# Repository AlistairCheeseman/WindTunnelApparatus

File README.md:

# WindTunnelApparatus
MENG Data Acquisition + motion control for Wind Tunnel Apparatus Project

There are three root folders in this repository:

Hardware  -  Contains hardware designs, files are created in KiCAD however relevant pdfs are provided.

Software  -  Contains software used on the Acquisition Computer

Firmware  -  Contains firmware source code, self explanatory

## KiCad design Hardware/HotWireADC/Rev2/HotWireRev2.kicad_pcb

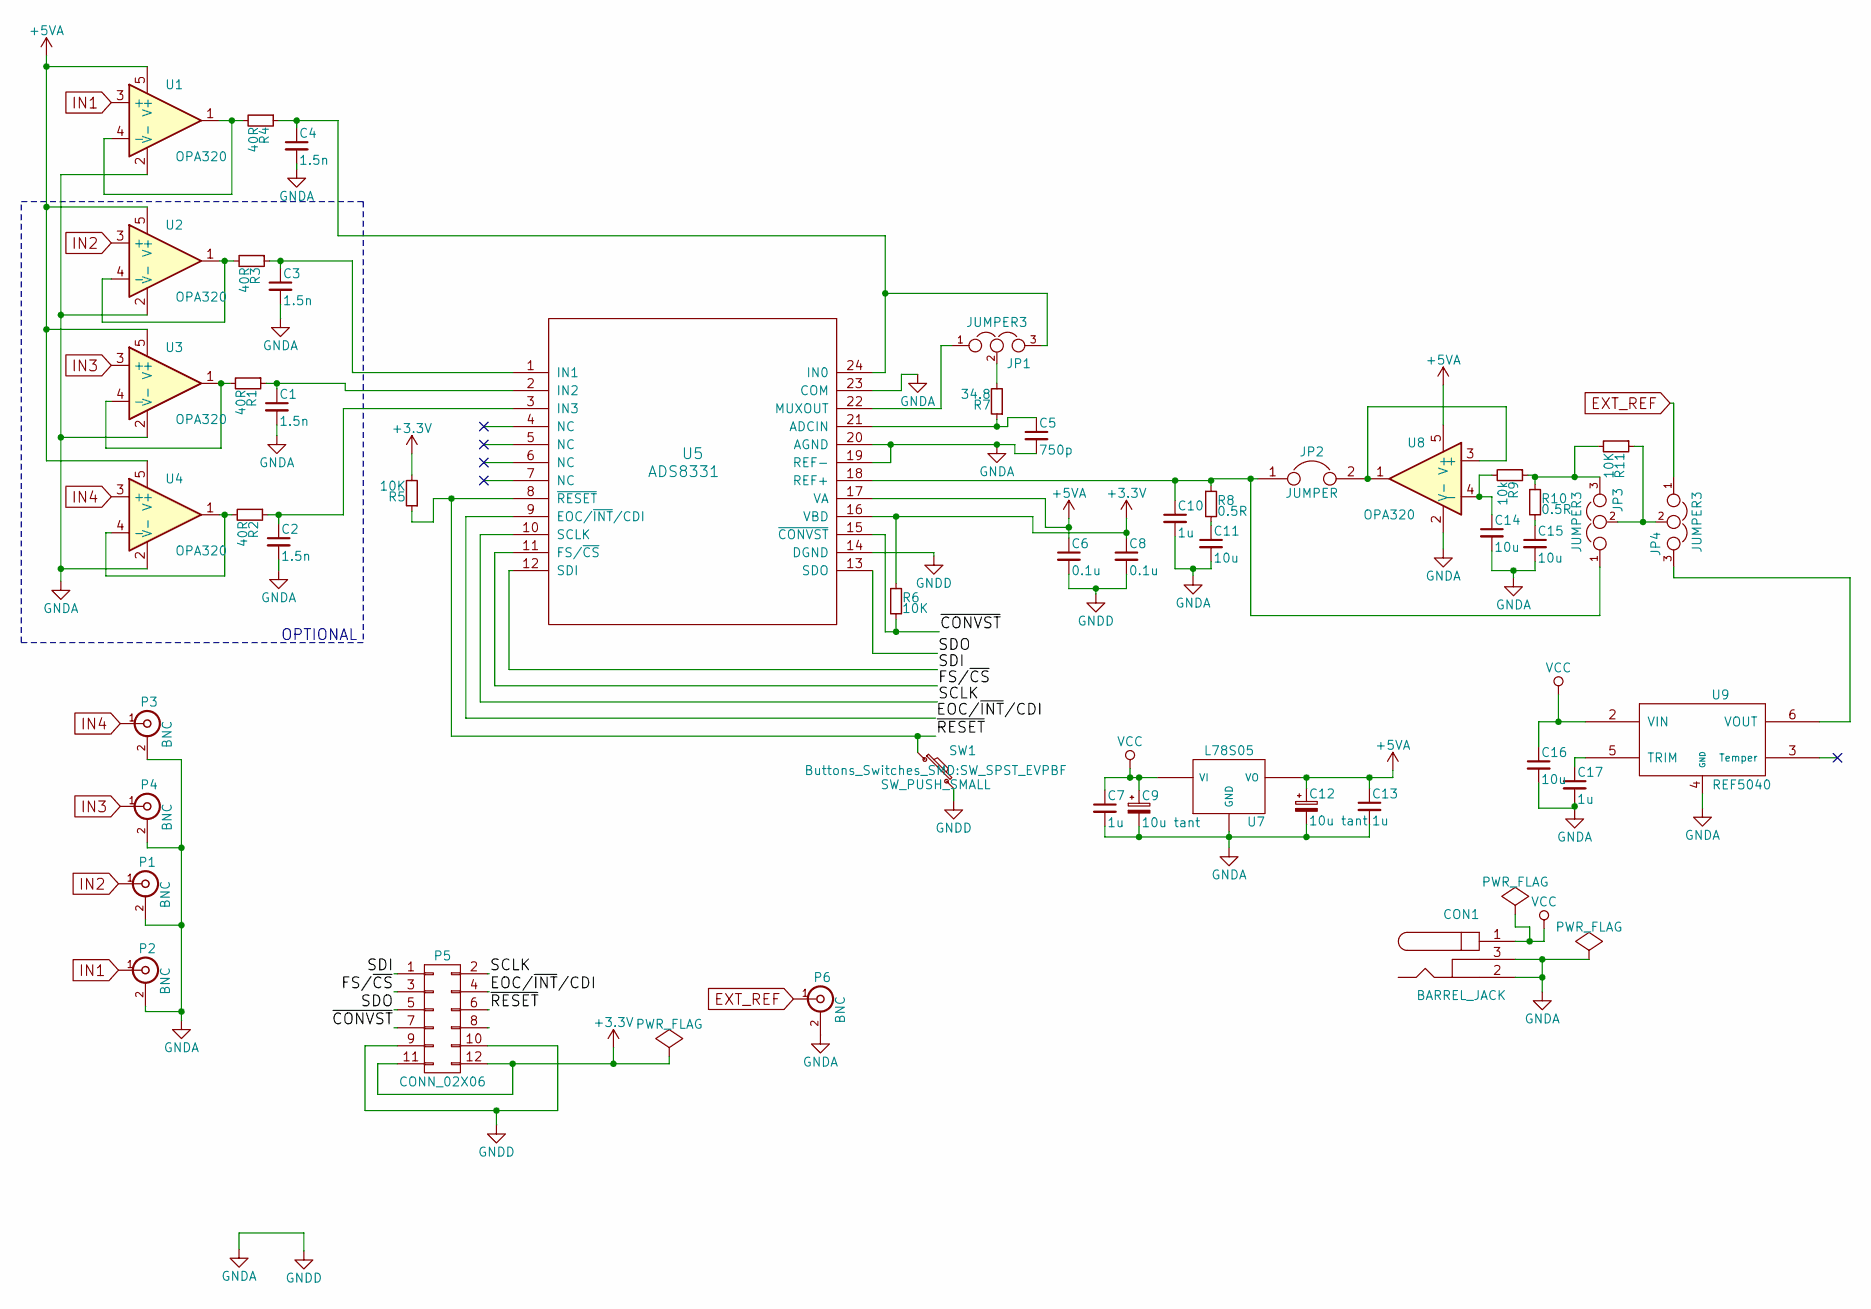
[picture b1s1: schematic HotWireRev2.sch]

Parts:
C1, C2, C3, C4: 1.5n; C_1206_HandSoldering
C5: 750p; C_1206_HandSoldering
C6, C8: 0.1u; C_1206_HandSoldering
C7, C10, C13, C17: 1u; C_1206_HandSoldering
C9, C12: 10u tant; TantalC_SizeU_EIA-6032
C11, C14, C15, C16: 10u; C_1206_HandSoldering
CON1: BARREL_JACK; JACK_SMD
JP1, JP3, JP4: JUMPER3; Socket_Strip_Straight_1x03
JP2: JUMPER; Socket_Strip_Straight_1x02
P1, P2, P3, P4, P6: BNC; bnc-ci
P5: CONN_02X06; Socket_Strip_Straight_2x06
R1, R2, R3, R4: 40R; R_1206_HandSoldering
R5, R6, R11: 10K; R_1206_HandSoldering
R7: 34.8; R_1206_HandSoldering
R8, R10: 0.5R; R_1206_HandSoldering
R9: 10k; R_1206_HandSoldering
SW1: SW_PUSH_SMALL; SW_SPST_EVPBF
U1, U2, U3, U4, U8: OPA320; SOT-23-5
U5: ADS8331; TSSOP-24_4.4x7.8mm_Pitch0.65mm
U7: L78S05; TO-220_REGULATORVIGNDVO_Vertical_LargePads
U9: REF5040; SOIC-8-N

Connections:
+3V3: C8.1, P5.11, P5.12, R5.2, R6.1, U5.16 (VBD)
+5VA: C6.1, C12.1, C13.1, U1.5 (V+), U2.5 (V+), U3.5 (V+), U4.5 (V+), U5.17 (VA), U7.VO, U8.5 (V+)
/EOC/~INT~/CDI: P5.4, U5.9 (EOC/~INT~/CDI)
/FS/~CS: P5.3, U5.11 (FS/~CS)
/SCLK: P5.2, U5.10 (SCLK)
/SDI: P5.1, U5.12 (SDI)
/SDO: P5.5, U5.13 (SDO)
/~CONVST: P5.7, R6.2, U5.15 (~CONVST)
/~RESET: P5.6, R5.1, SW1.1, U5.8 (~RESET)
EXT_REF: JP4.1, P6.1 (In)
GNDA: C1.2, C2.2, C3.2, C4.2, C5.2, C6.2, C7.2, C8.2, C9.2, C10.2, C11.2, C12.2, C13.2, C14.2, C15.2, C16.2, C17.2, CON1.2, CON1.3, P1.2 (Ext), P2.2 (Ext), P3.2 (Ext), P4.2 (Ext), P5.9, P5.10, P6.2 (Ext), SW1.2, U1.2 (V-), U2.2 (V-), U3.2 (V-), U4.2 (V-), U5.14 (DGND), U5.19 (REF-), U5.20 (AGND), U5.23 (COM), U7.GND, U8.2 (V-), U9.4 (GND)
IN1: P2.1 (In), U1.3 (+)
IN2: P1.1 (In), U2.3 (+)
IN3: P4.1 (In), U3.3 (+)
IN4: P3.1 (In), U4.3 (+)
unnamed: C1.1, R1.1, U5.2 (IN2)
unnamed: C2.1, R2.1, U5.3 (IN3)
unnamed: C3.1, R3.1, U5.1 (IN1)
unnamed: C4.1, JP1.3, R4.1, U5.24 (IN0)
unnamed: C5.1, R7.1, U5.21 (ADCIN)
unnamed: C10.1, JP2.1, JP3.1, R8.1, U5.18 (REF+)
unnamed: C11.1, R8.2
unnamed: C14.1, R9.2, U8.4 (-)
unnamed: C15.1, R10.2
unnamed: C17.1, U9.5 (TRIM)
unnamed: JP1.1, U5.22 (MUXOUT)
unnamed: JP1.2, R7.2
unnamed: JP2.2, U8.1, U8.3 (+)
unnamed: JP3.2, JP4.2, R11.1
unnamed: JP3.3, R9.1, R10.1, R11.2
unnamed: JP4.3, U9.6 (VOUT)
unnamed: R1.2, U3.1, U3.4 (-)
unnamed: R2.2, U4.1, U4.4 (-)
unnamed: R3.2, U2.1, U2.4 (-)
unnamed: R4.2, U1.1, U1.4 (-)
VCC: C7.1, C9.1, C16.1, CON1.1, U7.VI, U9.2 (VIN)

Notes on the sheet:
OPTIONAL

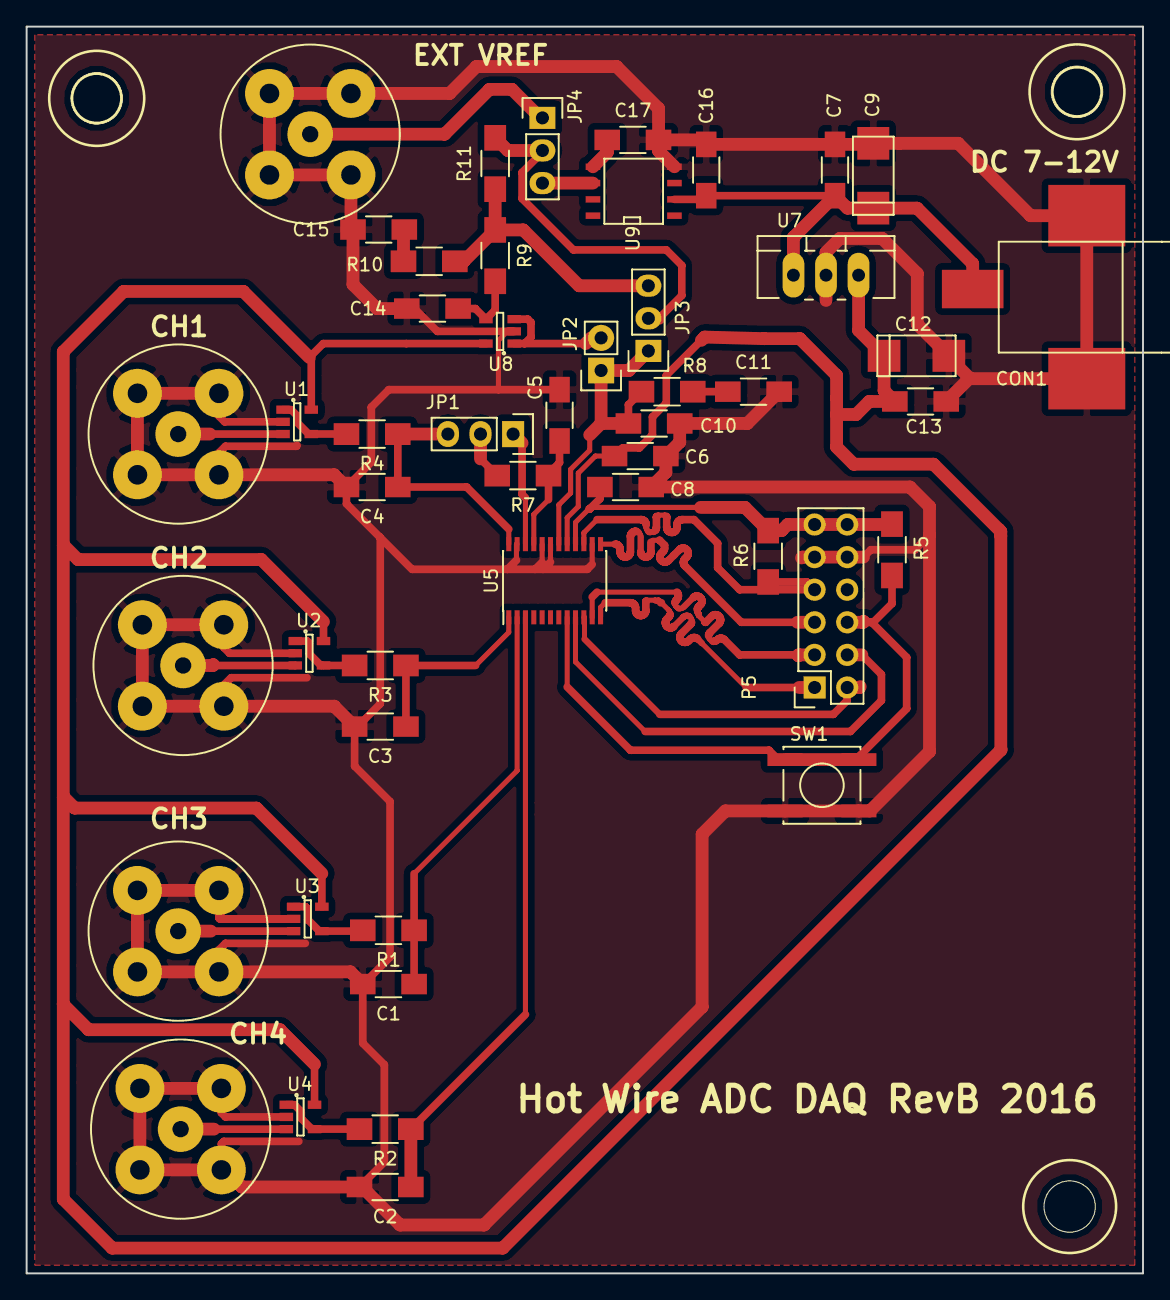
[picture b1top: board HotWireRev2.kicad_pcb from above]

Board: 2 copper layers, 87.0 x 97.2 mm, 48 parts (0 on the bottom side), 36 nets.

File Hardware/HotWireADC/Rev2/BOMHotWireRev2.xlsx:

Reference | Value | Footprint | Datasheet
U5 | ADS8331 | Housings_SSOP:TSSOP-24_4.4x7.8mm_Pitch0.65mm
JP1 | JUMPER3 | Socket_Strips:Socket_Strip_Straight_1x03 |  |  |  |  |  | Mouser Part No | Mouser Link
U1 | OPA320 | TO_SOT_Packages_SMD:SOT-23-5 |  |  |  | ADS8331 | 1 | 595-ADS8331IPW | http://www.mouser.co.uk/Search/ProductDetail.aspx?R=ADS8331I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
U2 | OPA320 | TO_SOT_Packages_SMD:SOT-23-5 |  |  |  | OPA320 | 5 | 595-OPA320AIDBVR | http://www.mouser.co.uk/Search/ProductDetail.aspx?R=OPA320AI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
U3 | OPA320 | TO_SOT_Packages_SMD:SOT-23-5 |  |  |  | 40R | 4 | #NAME?
U4 | OPA320 | TO_SOT_Packages_SMD:SOT-23-5 |  |  |  | 1.5n | 4 | 77-VJ1206Y152KXXCBC | http://www.mouser.co.uk/Search/ProductDetail.aspx?R=VJ1206Y1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
R4 | 40R | Resistors_SMD:R_1206_HandSoldering |  |  |  | 10K | 4 | 71-CRCW1206-10K-E3 | http://www.mouser.co.uk/Search/ProductDetail.aspx?R=CRCW1206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
C4 | 1.5n | Capacitors_SMD:C_1206_HandSoldering |  |  |  | 34.799999999999997 | 1 | 667-ERJ-8ENF34R8V | http://www.mouser.co.uk/Search/ProductDetail.aspx?R=ERJ-8ENF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
R3 | 40R | Resistors_SMD:R_1206_HandSoldering |  |  |  | 750p | 1 | 581-12065A751JAT2A | http://www.mouser.co.uk/Search/ProductDetail.aspx?R=12065A75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
C3 | 1.5n | Capacitors_SMD:C_1206_HandSoldering |  |  |  | SW_PUSH_SMALL | 1 | 506-2-1437565-8 | http://www.mouser.co.uk/Search/ProductDetail.aspx?R=2-143756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
R1 | 40R | Resistors_SMD:R_1206_HandSoldering |  |  |  | 0.1u | 2 | 77-VJ1206Y104KXBAT | http://www.mouser.co.uk/Search/ProductDetail.aspx?R=VJ1206Y1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
C1 | 1.5n | Capacitors_SMD:C_1206_HandSoldering |  |  |  | 1u | 4 | 77-VJ1206Y105KXQTBC | http://www.mouser.co.uk/Search/ProductDetail.aspx?R=VJ1206Y1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
R2 | 40R | Resistors_SMD:R_1206_HandSoldering |  |  |  | 10u | 4 | 77-VJ1206V106ZXQTBC | http://www.mouser.co.uk/Search/ProductDetail.aspx?R=VJ1206V1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
C2 | 1.5n | Capacitors_SMD:C_1206_HandSoldering |  |  |  | 0.5R | 2 | 603-RL1206FR070R5L | http://www.mouser.co.uk/Search/ProductDetail.aspx?R=RL1206FR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
R5 | 10K | Resistors_SMD:R_1206_HandSoldering |  |  |  | REF5040 | 1 | 595-REF5040AIDR | http://www.mouser.co.uk/Search/ProductDetail.aspx?R=REF5040A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
R7 | 34.799999999999997 | Resistors_SMD:R_1206_HandSoldering |  |  |  | 10u tant | 2 | 647-F931A106MAA | http://www.mouser.co.uk/Search/ProductDetail.aspx?R=F931A106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
C5 | 750p | Capacitors_SMD:C_1206_HandSoldering |  |  |  | L78S05 | 1 | 511-L78S05CV | http://www.mouser.co.uk/Search/ProductDetail.aspx?R=L78S05CV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
R6 | 10K | Resistors_SMD:R_1206_HandSoldering |  |  |  | BNC | 5 | 571-5-1634503-1 | http://www.mouser.co.uk/Search/ProductDetail.aspx?R=5-163450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
SW1 | SW_PUSH_SMALL | Buttons_Switches_SMD:SW_SPST_EVPBF |  |  |  | BARREL_JACK | 1 | 502-RASM712X | http://www.mouser.co.uk/Search/ProductDetail.aspx?R=RASM712X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
C8 | 0.1u | Capacitors_SMD:C_1206_HandSoldering
C6 | 0.1u | Capacitors_SMD:C_1206_HandSoldering
C10 | 1u | Capacitors_SMD:C_1206_HandSoldering
C11 | 10u | Capacitors_SMD:C_1206_HandSoldering |  |  |  | Extra filter
R8 | 0.5R | Resistors_SMD:R_1206_HandSoldering |  |  |  | 22u | 1 | 581-1206ZG226ZAT2A
JP4 | JUMPER3 | Socket_Strips:Socket_Strip_Straight_1x03 |  |  |  | 0.22Ohm | 1 | 279-RL73K2BR22JTD
JP3 | JUMPER3 | Socket_Strips:Socket_Strip_Straight_1x03
JP2 | JUMPER | Socket_Strips:Socket_Strip_Straight_1x02
U8 | OPA320 | TO_SOT_Packages_SMD:SOT-23-5 |  |  |  | Kostas BNC connector |  | 571-1-1337543-0
C14 | 10u | Capacitors_SMD:C_1206_HandSoldering
R10 | 0.5R | Resistors_SMD:R_1206_HandSoldering |  |  |  | 100ohm |  | 594-53611101
C15 | 10u | Capacitors_SMD:C_1206_HandSoldering |  |  |  | 1k |  | 858-P160KN0QD15B1K
R9 | 10k | Resistors_SMD:R_1206_HandSoldering |  |  |  | 20k |  | 858-P160KN-0QC15B20K
R11 | 10K | Resistors_SMD:R_1206_HandSoldering
U9 | REF5040 | SMD_Packages:SOIC-8-N |  |  |  | knob for pot |  | 652-H-22-6A
C17 | 1u | Capacitors_SMD:C_1206_HandSoldering
C16 | 10u | Capacitors_SMD:C_1206_HandSoldering |  |  | Rapid part no
C9 | 10u tant | Capacitors_Tantalum_SMD:TantalC_SizeU_EIA-6032 |  |  | 11-3438 | 4.7nF |  | 810-FG18X7R1H472KNT0 | http://www.mouser.co.uk/ProductDetail/TDK/FG18X7R1H472KNT00/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
C12 | 10u tant | Capacitors_Tantalum_SMD:TantalC_SizeU_EIA-6032 |  |  | 11-3436 | 2.2nf |  | 810-FG18C0G1H222JNT6 | http://www.mouser.co.uk/ProductDetail/TDK/FG18C0G1H222JNT06/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
C13 | 1u | Capacitors_SMD:C_1206_HandSoldering |  |  | 11-3433 | 470pf |  | 810-FG18C0G1H471JNT6 | http://www.mouser.co.uk/ProductDetail/TDK/FG18C0G1H471JNT06/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
C7 | 1u | Capacitors_SMD:C_1206_HandSoldering |  |  | 11-3431 | 220pf |  | 810-FG18C0G1H221JNT6 | http://www.mouser.co.uk/ProductDetail/TDK/FG18C0G1H221JNT06/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
U7 | L78S05 | CustomFootprints:TO-220_REGULATORVIGNDVO_Vertical_LargePads |  |  | 11-3409 | 150pf |  | 810-FG18C0G1H151JNT0 | http://www.mouser.co.uk/ProductDetail/TDK/FG18C0G1H151JNT00/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
P3 | BNC | Connect:bnc-ci
P4 | BNC | Connect:bnc-ci
P1 | BNC | Connect:bnc-ci
P2 | BNC | Connect:bnc-ci |  |  |  | LM555CN |  | 512-LM555CN | http://www.mouser.co.uk/ProductDetail/Fairchild-Semiconducto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
P5 | CONN_02X06 | Socket_Strips:Socket_Strip_Straight_2x06
CON1 | BARREL_JACK | Connect:JACK_ALIM
P6 | BNC | Connect:bnc-ci

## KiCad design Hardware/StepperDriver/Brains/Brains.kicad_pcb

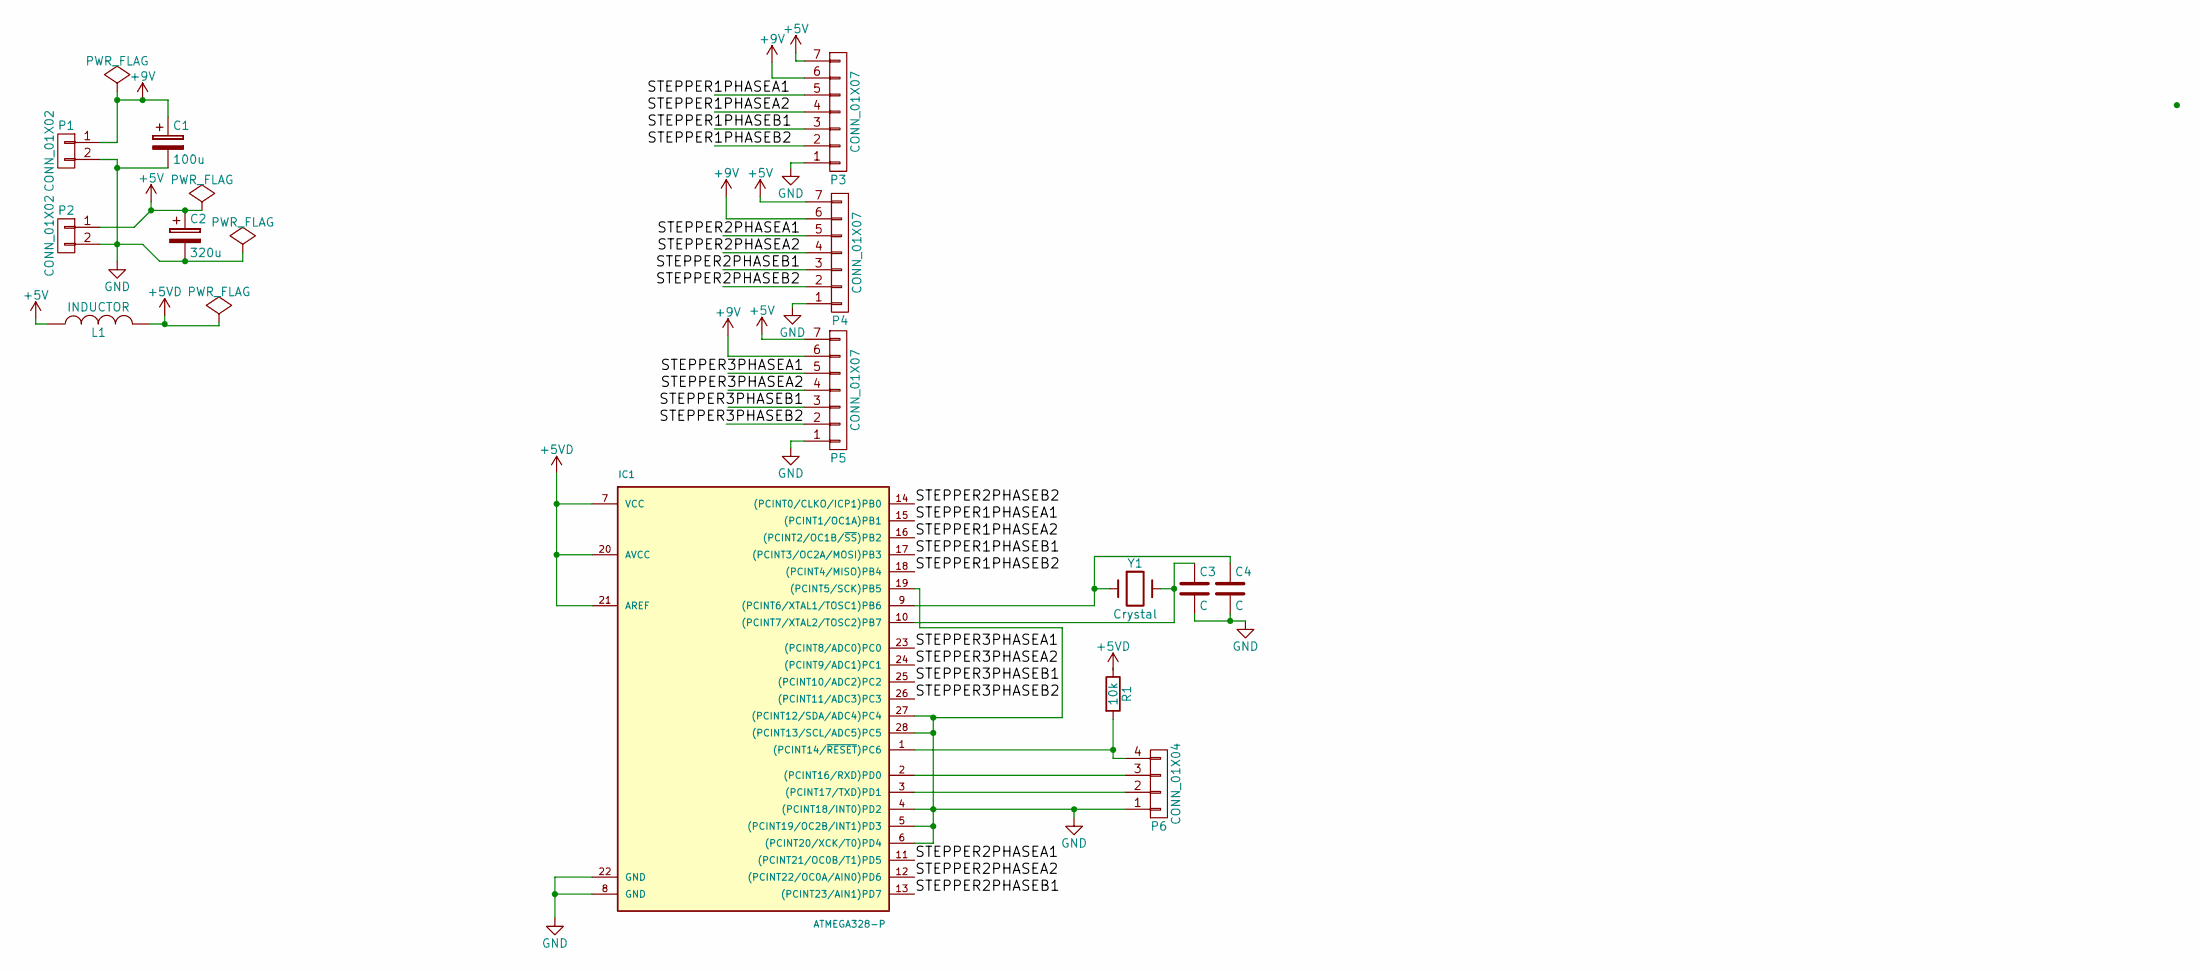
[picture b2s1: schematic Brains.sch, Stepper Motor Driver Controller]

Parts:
C1: 100u; C_Radial_D10_L20_P7.5
C2: 320u; C_Radial_D10_L20_P7.5
C3, C4: C; C_Disc_D3_P2.5
IC1: ATMEGA328-P; DIP-28_W7.62mm_LongPads
L1: INDUCTOR; Neosid_Inductor_Sd12k-style3
P1: CONN_01X02; TerminalBlock_Pheonix_MPT-2.54mm_2pol
P2: CONN_01X02; WAGO_734_2pin_Straight_RuggedPads
P3, P4, P5: CONN_01X07; Pin_Header_Straight_1x07
P6: CONN_01X04; TerminalBlock_Pheonix_MPT-2.54mm_4pol
R1: 10k; Resistor_Horizontal_RM10mm
Y1: Crystal; Crystal_HC49-U_Vertical

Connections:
+5V: C2.1, L1.1, P2.1, P3.7, P4.7, P5.7
+5VD: IC1.7 (VCC), IC1.20 (AVCC), IC1.21 (AREF), L1.2, R1.1
+9V: C1.1, P1.1, P3.6, P4.6, P5.6
/STEPPER1PHASEA1: IC1.15 ((PCINT1/OC1A)PB1), P3.5
/STEPPER1PHASEA2: IC1.16 ((PCINT2/OC1B/~SS~)PB2), P3.4
/STEPPER1PHASEB1: IC1.17 ((PCINT3/OC2A/MOSI)PB3), P3.3
/STEPPER1PHASEB2: IC1.18 ((PCINT4/MISO)PB4), P3.2
/STEPPER2PHASEA1: IC1.11 ((PCINT21/OC0B/T1)PD5), P4.5
/STEPPER2PHASEA2: IC1.12 ((PCINT22/OC0A/AIN0)PD6), P4.4
/STEPPER2PHASEB1: IC1.13 ((PCINT23/AIN1)PD7), P4.3
/STEPPER2PHASEB2: IC1.14 ((PCINT0/CLKO/ICP1)PB0), P4.2
/STEPPER3PHASEA1: IC1.23 ((PCINT8/ADC0)PC0), P5.5
/STEPPER3PHASEA2: IC1.24 ((PCINT9/ADC1)PC1), P5.4
/STEPPER3PHASEB1: IC1.25 ((PCINT10/ADC2)PC2), P5.3
/STEPPER3PHASEB2: IC1.26 ((PCINT11/ADC3)PC3), P5.2
GND: C1.2, C2.2, C3.2, C4.2, IC1.4 ((PCINT18/INT0)PD2), IC1.5 ((PCINT19/OC2B/INT1)PD3), IC1.6 ((PCINT20/XCK/T0)PD4), IC1.8 (GND), IC1.19 ((PCINT5/SCK)PB5), IC1.22 (GND), IC1.27 ((PCINT12/SDA/ADC4)PC4), IC1.28 ((PCINT13/SCL/ADC5)PC5), P1.2, P2.2, P3.1, P4.1, P5.1, P6.1
unnamed: C3.1, IC1.10 ((PCINT7/XTAL2/TOSC2)PB7), Y1.2
unnamed: C4.1, IC1.9 ((PCINT6/XTAL1/TOSC1)PB6), Y1.1
unnamed: IC1.1 ((PCINT14/~RESET~)PC6), P6.4, R1.2
unnamed: IC1.2 ((PCINT16/RXD)PD0), P6.3
unnamed: IC1.3 ((PCINT17/TXD)PD1), P6.2

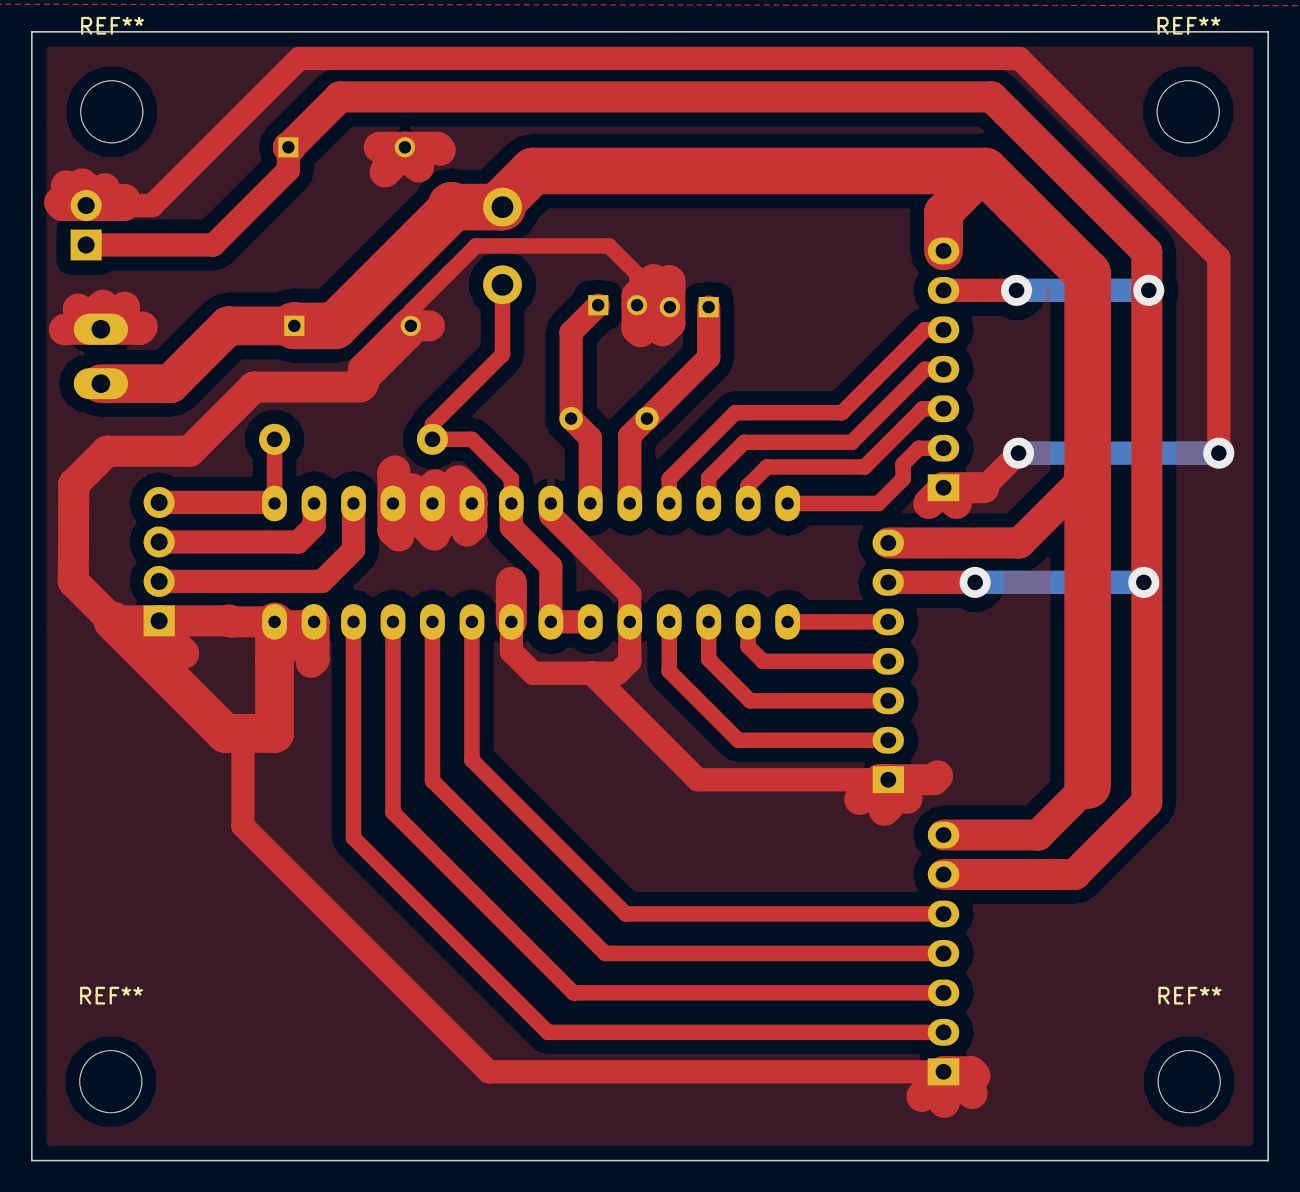
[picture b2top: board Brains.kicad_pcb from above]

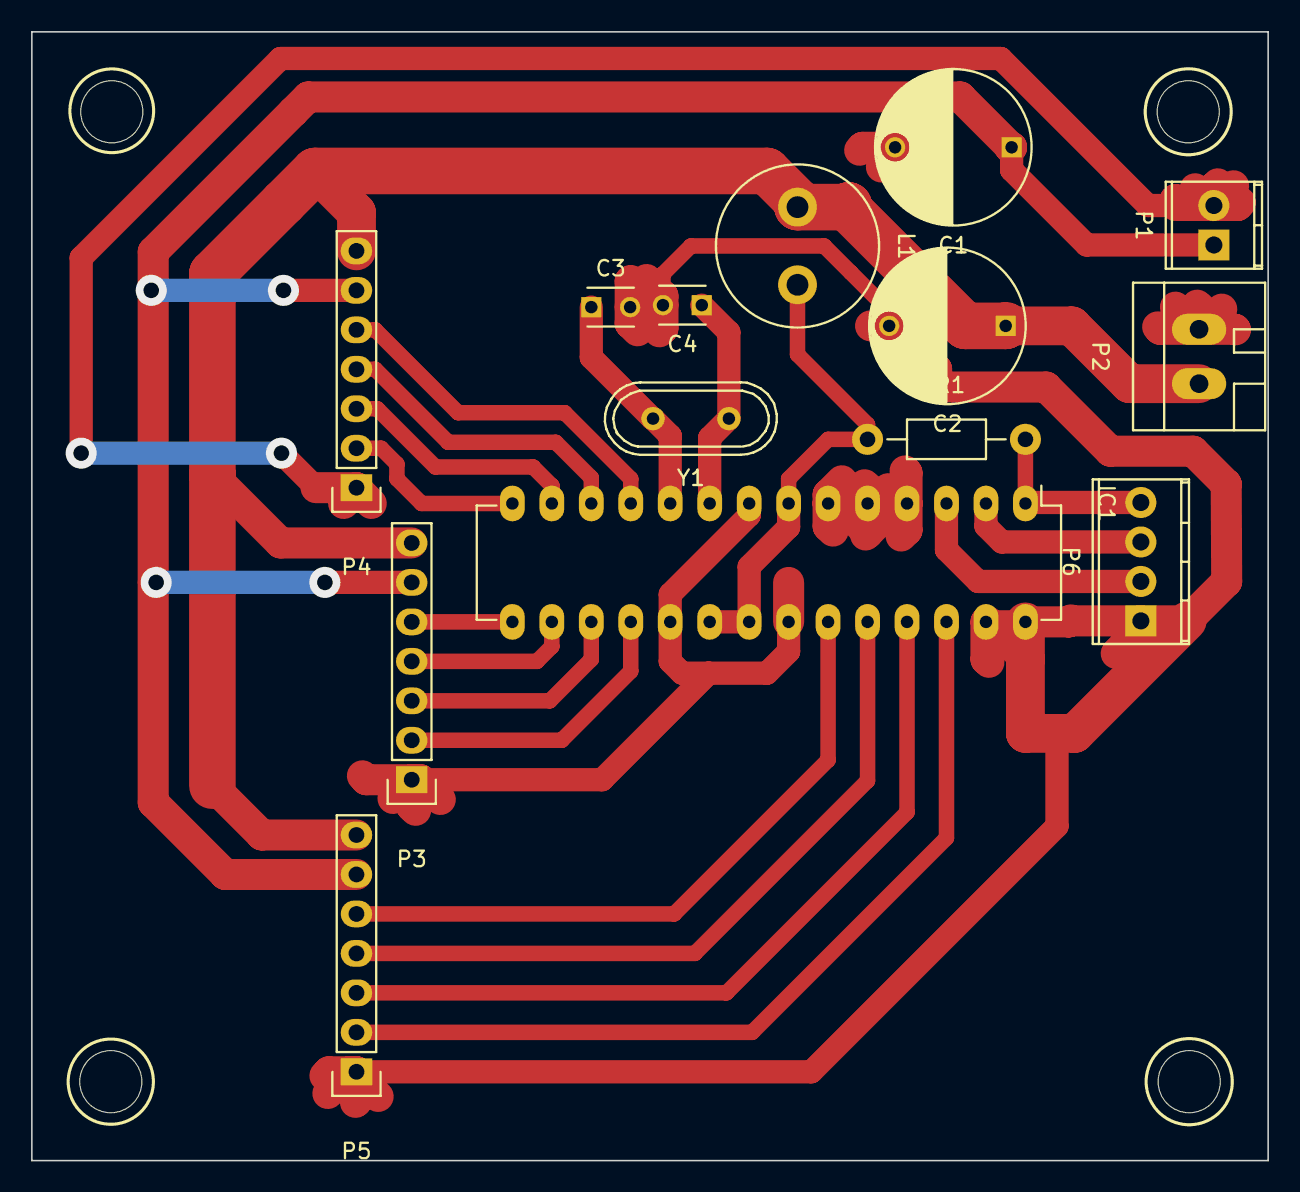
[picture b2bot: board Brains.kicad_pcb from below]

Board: 2 copper layers, 79.6 x 72.6 mm, 14 parts (14 on the bottom side), 21 nets.

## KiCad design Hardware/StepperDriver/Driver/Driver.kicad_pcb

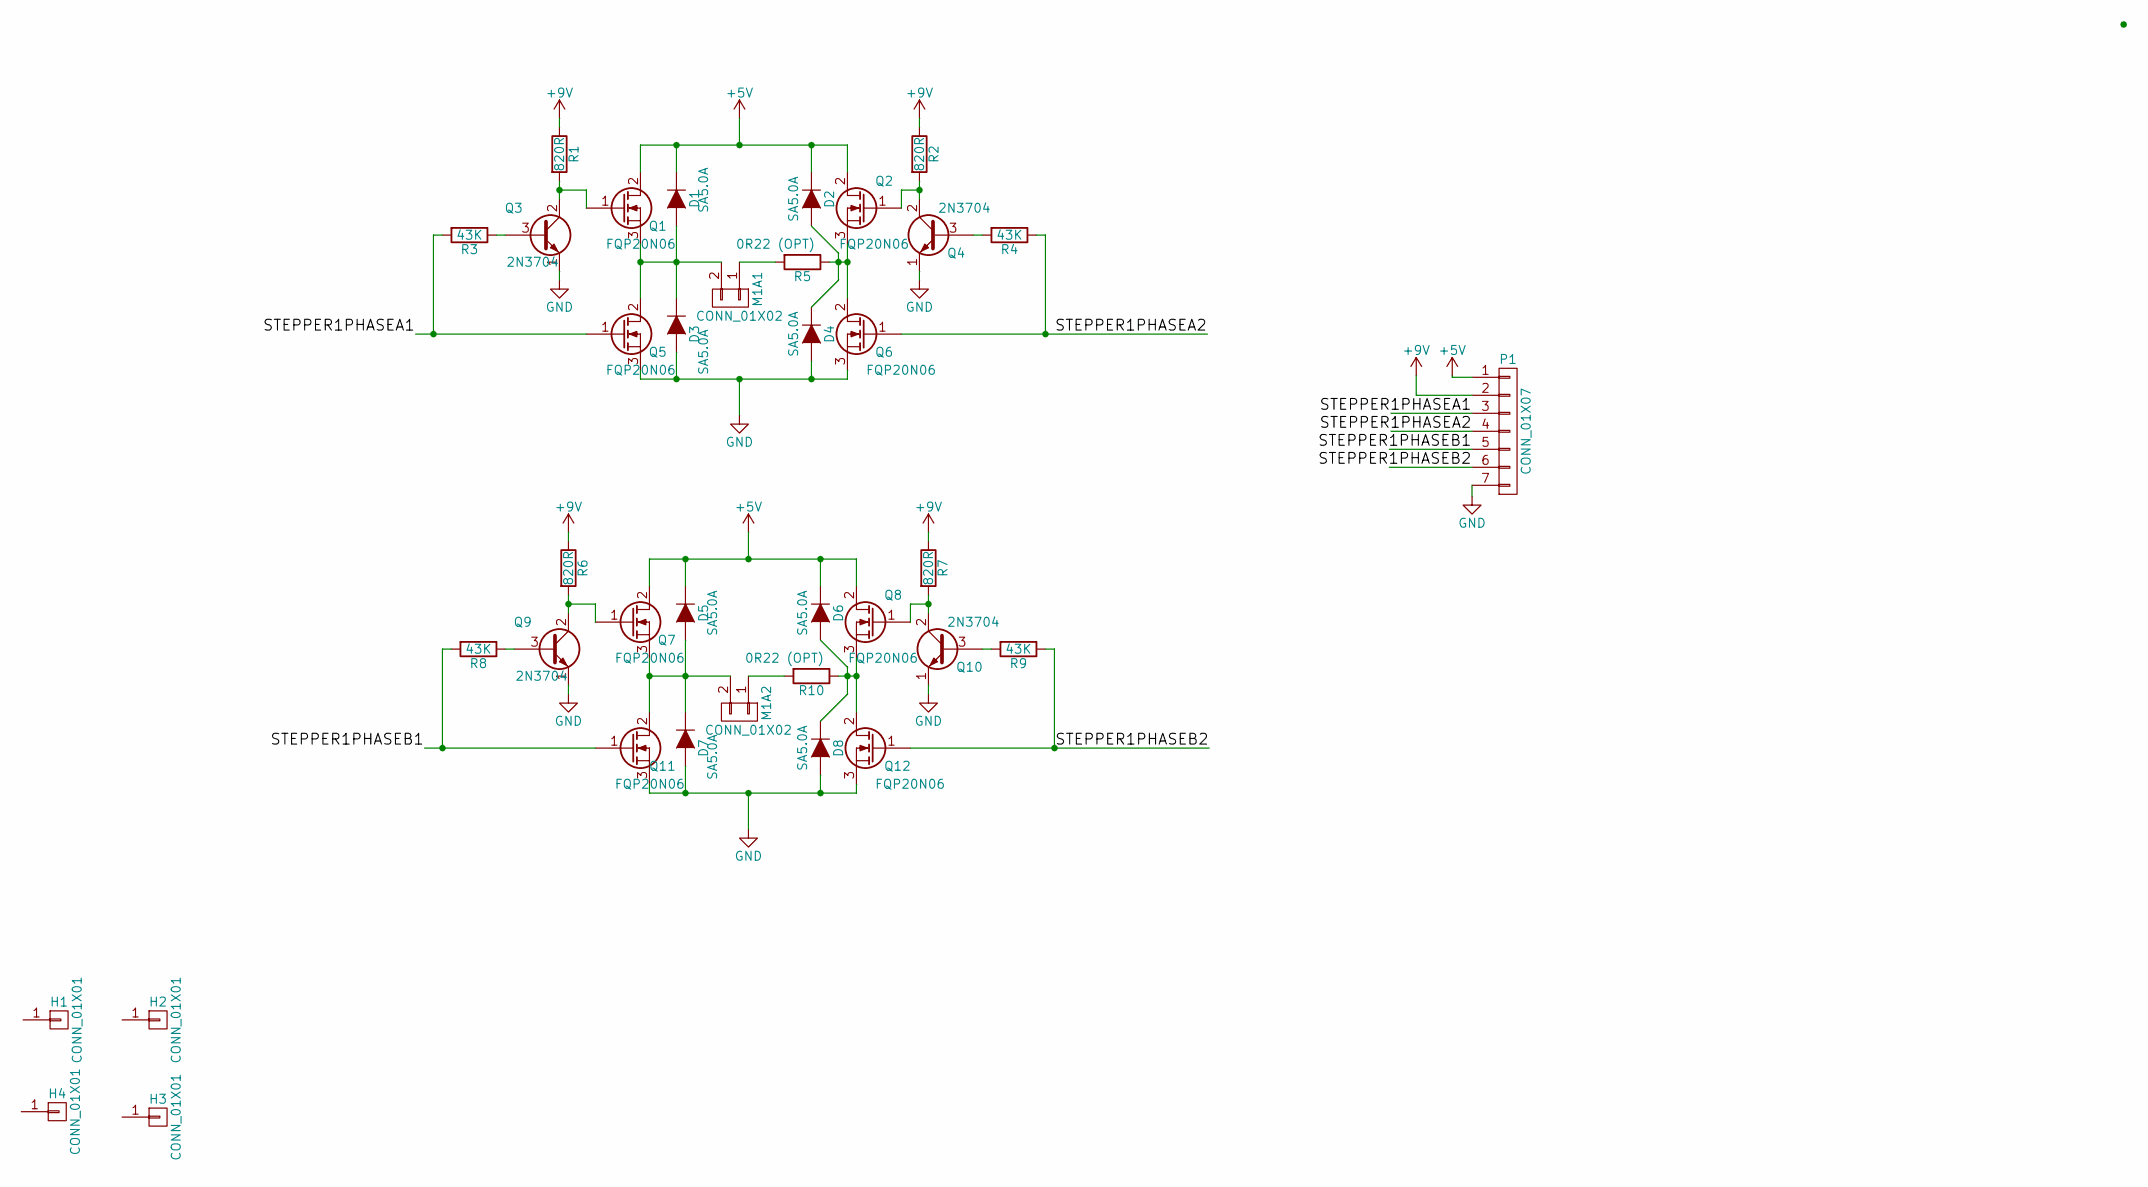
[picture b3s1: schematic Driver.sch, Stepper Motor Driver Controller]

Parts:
D1, D2, D3, D4, D5, D6, D7, D8: SA5.0A; Diode_DO-201AD_Horizontal_RM15
H1, H2, H3, H4: CONN_01X01; MountingHole_4mm
M1A1, M1A2: CONN_01X02; TerminalBlock_Pheonix_MPT-2.54mm_2pol
P1: CONN_01X07; Pin_Header_Straight_1x07
Q1, Q2, Q5, Q6, Q7, Q8, Q11, Q12: FQP20N06; TO-220_Neutral123_Horizontal_Reverse_LargePads
Q3, Q4, Q9, Q10: 2N3704; TO-92_Molded_Wide
R1, R2, R6, R7: 820R; Resistor_Horizontal_RM10mm
R3, R4, R8, R9: 43K; Resistor_Horizontal_RM10mm
R5, R10: 0R22 (OPT); Resistor_Cement_KOA-BGR-3N

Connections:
+5V: D1.1 (K), D2.1 (K), D5.1 (K), D6.1 (K), P1.1, Q1.2 (D), Q2.2 (D), Q7.2 (D), Q8.2 (D)
+9V: P1.2, R1.1, R2.1, R6.1, R7.1
/STEPPER1PHASEA1: P1.3, Q5.1 (G), R3.2
/STEPPER1PHASEA2: P1.4, Q6.1 (G), R4.1
/STEPPER1PHASEB1: P1.5, Q11.1 (G), R8.2
/STEPPER1PHASEB2: P1.6, Q12.1 (G), R9.1
GND: D3.2 (A), D4.2 (A), D7.2 (A), D8.2 (A), P1.7, Q3.1 (E), Q4.1 (E), Q5.3 (S), Q6.3 (S), Q9.1 (E), Q10.1 (E), Q11.3 (S), Q12.3 (S)
unnamed: D1.2 (A), D3.1 (K), M1A1.2, Q1.3 (S), Q5.2 (D)
unnamed: D2.2 (A), D4.1 (K), Q2.3 (S), Q6.2 (D), R5.1
unnamed: D5.2 (A), D7.1 (K), M1A2.2, Q7.3 (S), Q11.2 (D)
unnamed: D6.2 (A), D8.1 (K), Q8.3 (S), Q12.2 (D), R10.1
unnamed: M1A1.1, R5.2
unnamed: M1A2.1, R10.2
unnamed: Q1.1 (G), Q3.2 (C), R1.2
unnamed: Q2.1 (G), Q4.2 (C), R2.2
unnamed: Q3.3 (B), R3.1
unnamed: Q4.3 (B), R4.2
unnamed: Q7.1 (G), Q9.2 (C), R6.2
unnamed: Q9.3 (B), R8.1
unnamed: Q8.1 (G), Q10.2 (C), R7.2
unnamed: Q10.3 (B), R9.2

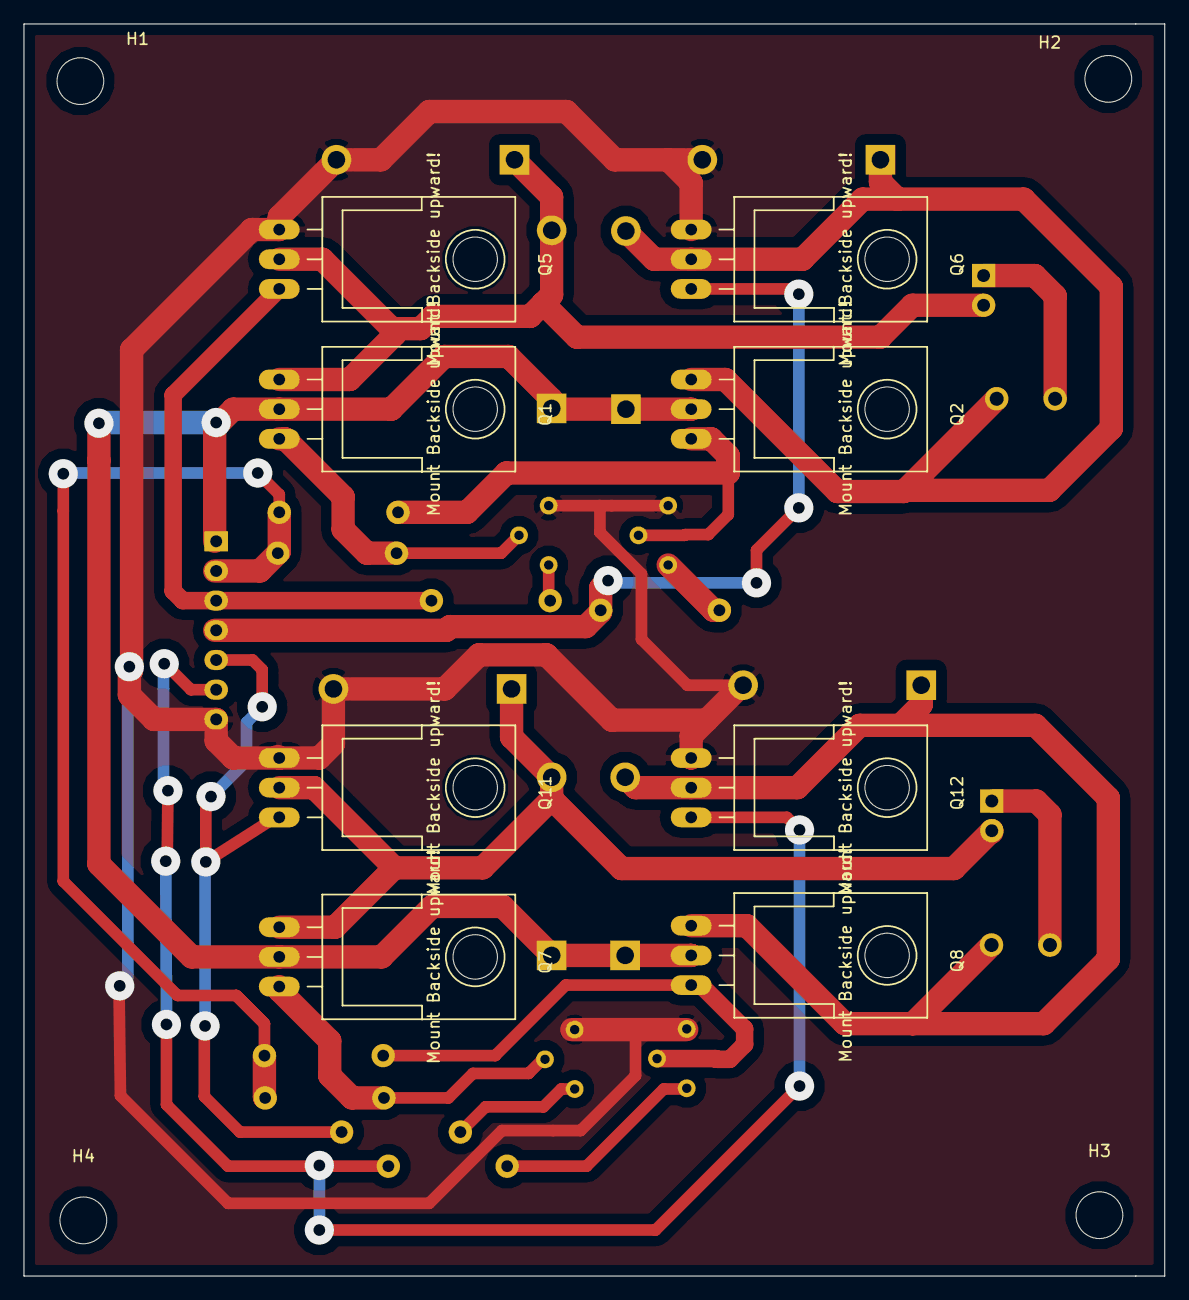
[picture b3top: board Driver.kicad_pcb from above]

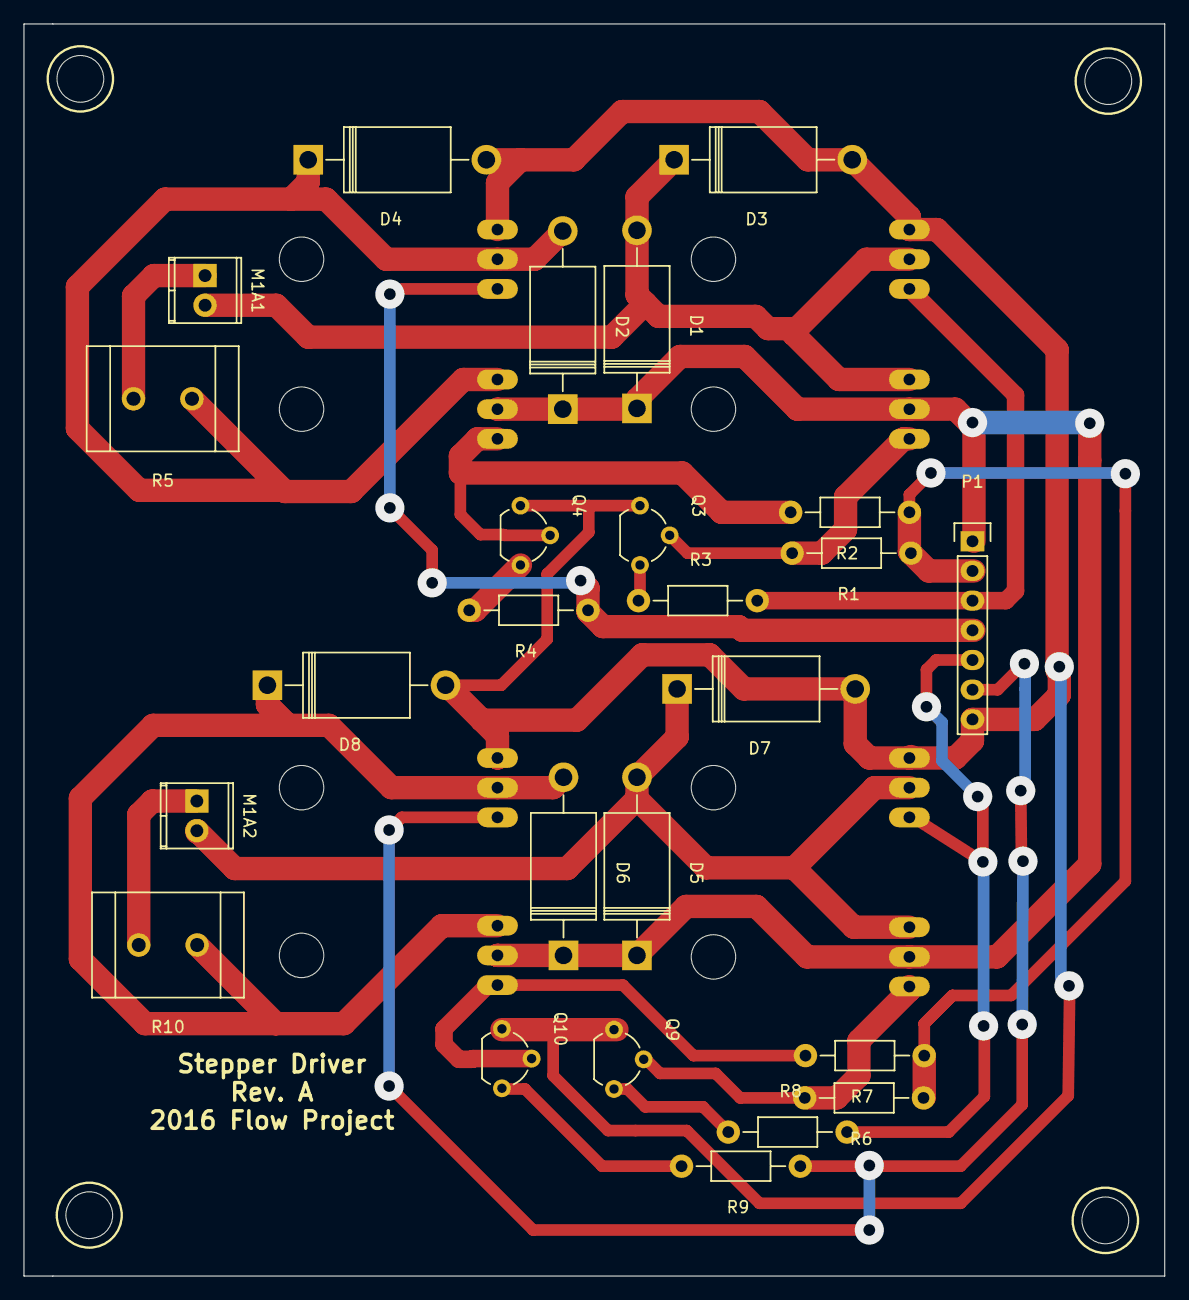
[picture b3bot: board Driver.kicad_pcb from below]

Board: 2 copper layers, 97.6 x 107.1 mm, 37 parts (25 on the bottom side), 21 nets.
